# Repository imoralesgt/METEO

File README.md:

# METEO
## TFM MSEEI Universidad de Malaga
## Iván René Morales Argueta - 2018

===========================================================

# ToDo List
## Meteo
- [x] Connect to MQTT Broker in object constructor
	* [x] Subscribe to each ```Settings``` sub-topic ```Settings/#```
	* [ ] \(Optional) _Show performance and broker info by subscribing to special $SYS topics (https://www.hivemq.com/blog/mqtt-essentials-part-5-mqtt-topics-best-practices)_
- [x] Sample each sensor using separate threads
	* [x] Create a generic sampling method (one-shot), which receives the sensor name as parameter
		- [x] ```sampleSensor (sensorName)```
		- [x] Front-end interface variables (i.e. Air Quality, instead of Humidity+Gas_Resistance)
	- [x] Create a thread/method to periodically launch the one-shot sampling method
	* [x] Generate as many threads running this method as required
	* [ ] ~~Kill sampling threads during object destruction~~ Destructor not compatible with threaded implementation
	* [X] Implement a mutual-exclusion mechanism to avoid access violations
- [x] Send sensors' data via MQTT using topics to distribute data into different channels
- [x] Each "METEO" station MUST have a vaild (integer type) identifier, starting from 0
- [x] Topics should accomplish with the following template:
	* [x] ```METEO/<stationNumber>/Data/<sensor>```
	* [x] Valid ```<stationNumber>``` (identifiers) are integers from 0 to N-1
	* [x] Valid ```<sensor>``` values are:
		- [x] Temperature (Environmental temperature) [temp]
		- [x] Humidity (Relative humidity) [hum]
		- [x] Pressure (Local atmospheric pressure) [pres]
		- [x] Light (Incident light measurement) [light]
		- [x] AirQuality (Air quality as pollution measurement) [airQ]
		- [ ] ~~PPM (Raw particle count) [ppm]~~ PPM is irrelevant. Instead, PPM field used to transmit raw gas resistance value
- [x] A special topic may be used to set/get the sampling period dymanically
	* [x] ```METEO/<stationNumber>/Settings/SamplingRate/<sensor>```
	* [x] ```<sensor>``` field (sub-topic) is the same as described before
	* [x] Sampling rate value must be validated to remain between a valid range
		- [x] Min sampling rate 1 minute
		- [x] Max sampling rate 120 minutes
		- [x] If a sampling rate (SR) out of these limits is set, a default value will be chosen if a prior valid SR wasn't set yet; otherwise, the last valid SR will remain active
- [ ] \(Optional) _A special topic may be used to remotely reboot the device if no Alive beacons have been received_
	- [ ] _```METEO/<stationNumber>/Setiings/Reboot```_
	- [ ] _A unique key must be sent as password (through ```Reboot``` topic) to force a reboot_
	- [ ] _Key will be ```stationNumber```-dependent and time-dependent (unix format) hash_
	- [ ] _Hash must be computed by UI_
- [x] A special topic may be used to announce "I'm Alive" messages from stations to broker
	* [x] Invoke it via a separate thread as it may behave as a locking method
	* [x] ```METEO/Alive```
	* [x] Each station should publish a message containing only its ```<stationNumber>``` periodically (ie. every 1 minute)

## Printed circuit board
- [x] Design a PCB to place the sensor boards and the User-Interaction hardware (push-button + LED)
	- [x] Design must be compatible with Raspberry PI 3 header footprint
	- [x] Power must be supplied from Raspberry PI's 3v3/GND breakout pins
	- [x] Manufacture PCB and test functionality

## BME680_METEO
- [x] Compute Air Quality (%) using Humidity and Gas measurements
- [ ] ~~Compute PPM using Gas Baseline and Gas measurements~~ Not a requirement. Discarded from further releases.

## User Interaction
- [x] Add an LED status indicator to show whether the server is running or not (using RPI-GPIO)
- [x] Add a push-button input to hard-reset the server via a separate thread if anything fails (using RPI-GPIO)

## Data management
- [x] Grab sensors' data from MQTT broker and process it to deliver filtered information 
- [x] Store the processed data into a SQLite database
- [x] Retreive data from Broker and append it to a table within in the DB (running in parallel thread?)
- [x] Export table's content to a CSV when required
- [x] If several measurements from different sensors retreived within the same MINUTE, store them in the same register row.
- [x] If several measurements form the same sensor retreived within the same MINUTE, average grabbed values and then store the last average computation.

## Reliability
- [x] Run meteo.py as a standalone application
	- [x] Set flag to meteo.py
		- [x] ```chmod +x meteo.py```
- [x] Autorun on boot
	- [x] ```sudo crontab -e```
	- [x] ```@reboot /home/pi/METEO/meteo.py &```
- [x] Software Watchdog Timer
	- [x] Run a parallel process (subscribed to ```ALIVE``` topic) to check whether METEO is running or not
	- [x] Restart METEO process after 3 consecutive ```ALIVE``` periods with no answer
	- [x] Start WDT timer after the first ```ALIVE``` message arrives

# User interface
- [x] Node-RED User Interface

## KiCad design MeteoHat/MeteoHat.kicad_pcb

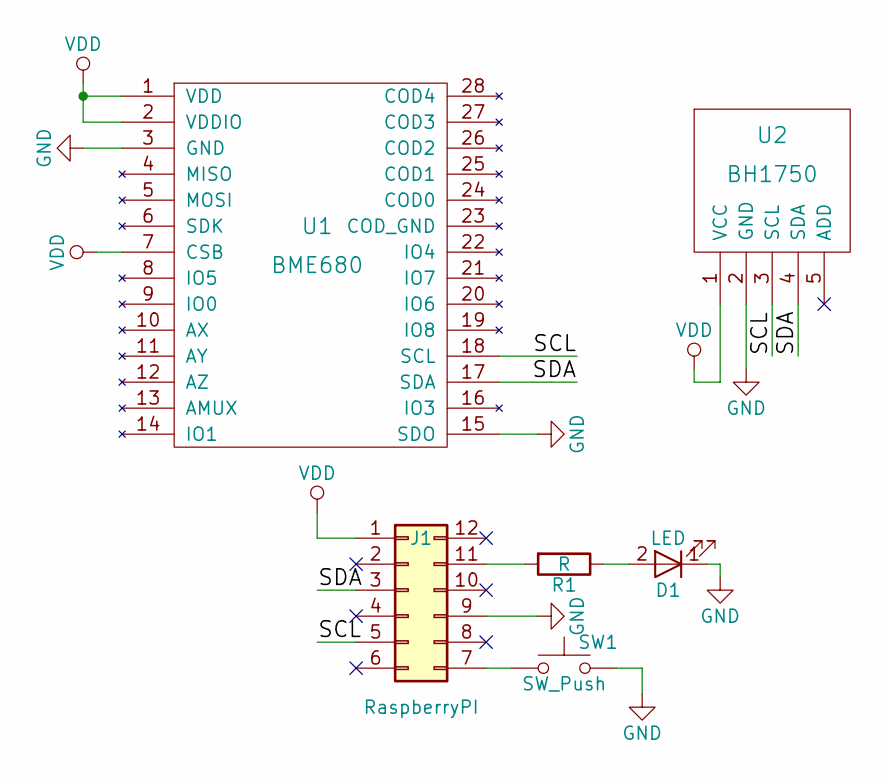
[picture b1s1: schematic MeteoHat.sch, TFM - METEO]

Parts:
D1: LED; LED_1206_HandSoldering
J1: RaspberryPI; Pin_Header_Straight_2x06_Pitch2.54mm
R1: R; R_0805_HandSoldering
SW1: SW_Push; 3x6x2.5mm_tact_switch
U1: BME680
U2: BH1750

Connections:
/SCL: J1.5, U1.18 (SCL), U2.3 (SCL)
/SDA: J1.3, U1.17 (SDA), U2.4 (SDA)
GND: D1.1 (K), J1.9, SW1.2, U1.3 (GND), U1.15 (SDO), U2.2 (GND)
unnamed: D1.2 (A), R1.1
unnamed: J1.7, SW1.1
unnamed: J1.11, R1.2
VDD: J1.1, U1.1 (VDD), U1.2 (VDDIO), U1.7 (CSB), U2.1 (VCC)

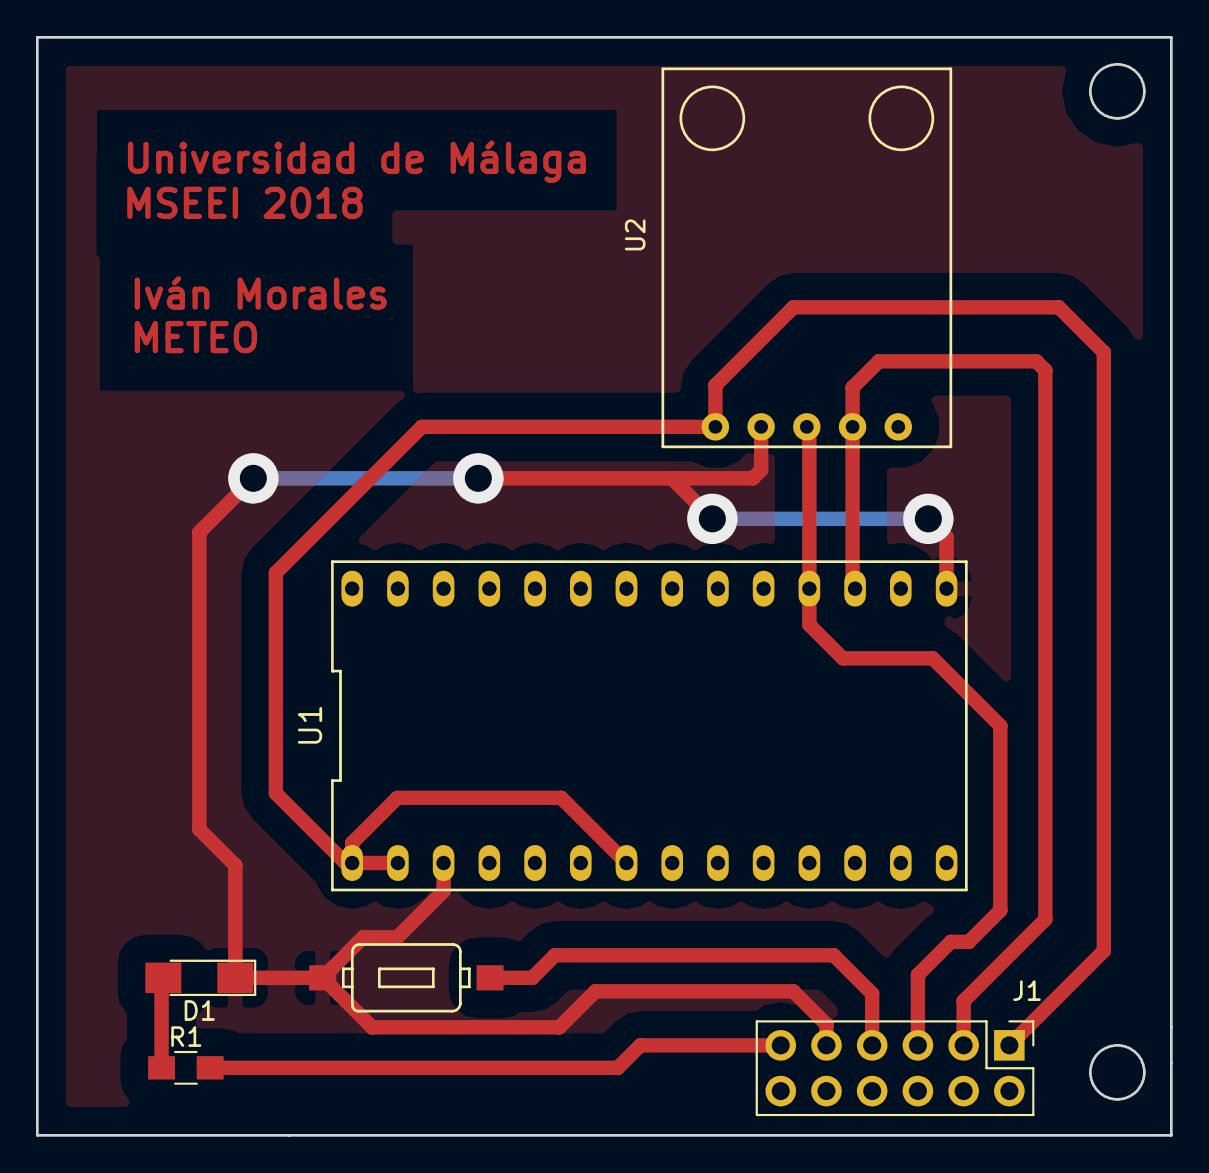
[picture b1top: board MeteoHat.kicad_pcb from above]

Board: 2 copper layers, 63.0 x 61.0 mm, 6 parts (0 on the bottom side), 7 nets.

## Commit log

2018-06-16 Initial repo setup
    Also added Sublime SFTP auto-upload config
2018-06-16 First BME680 test
    BME680 Interface Class for METEO first Test
2018-06-18 Added non-blocking gas sensor burn-in daemon
    - The rest of the sensors start measuring immediately after BME680 is initialized. Gas sensor is burned-up until burn-in time (default: 5 minutes) pass by.
    - Added external constants file for easy sensor configuration (sensorDefs.py).
    - Class was completely reordered to easily accomodate further changes in a much more robust and modular way.
2018-06-20 Moved class-related globals before constructor
2018-06-20 Added some comments
2018-06-20 Added light sensor import
2018-06-20 BH1750 low level library from oskar456
    https://gist.github.com/oskar456/95c66d564c58361ecf9f
2018-06-20 Added light sensor-related defines
2018-06-20 BH1750 Light sensor high level fault-tolerant library
    Default 0.5 lux resolution and 0x23 I2C Address Map
2018-06-23 Added Endline
2018-06-23 Added KeyboardInterrupt Exception handling in test mode
    Also added comments
2018-07-02 Work started under METEO main class
    - Requirements have been defined in the initial comments
    - Standarization of available sensors and sampling rate manipulation methods have been written
    - MQTT Client connection to broker has been implemented, including service restart if connection to broker fails
2018-07-12 Fixed some typos in the comments
2018-07-13 Added requirements to the TODO list
2018-07-14 PCB for Raspberry PI Hat
2018-07-14 Some minor tests done with MQTT Broker
2018-07-14 TODO list updated
2018-07-14 Fixed Readme format
2018-07-14 Fixed Readme tabs
2018-07-14 Added checkboxes to each item in the "ToDo" list
2018-07-14 Added optional requirements
2018-07-15 Fixed BME680 HAL to support threading
2018-07-15 Added some error definitions
2018-07-15 Implemented mutual-exclusion (MUTEX) mechanism
    - Implemented MUTEX with/without autoexecution of threads in queue
    - Mutex tests have been passed using a shared resource (BME680) in up to 20 (MAX_TASKS) concurrent threads where temperature was measured
    - Implemented one-shot measurement of front-end variables (temperature, air quality, ppm, presure, humidity, luminosity), which relay on back-end variables (gas resistor, thermometer, etc)
2018-07-16 Station number can be set in defs file
2018-07-16 MQTT Subscription/Publishing functionality added
    - Sampling rate can be individualy set for each sensor
    - Publishing sensor values still not working, mutex implemented and tested
2018-07-23 Fixed unsampled sensors Null data, now returning False if no sensor data available
2018-07-23 Sensor data published in separate threads as described in requirements
2018-07-24 Default sampling rate is now 5 minutes
2018-07-24 Debugging disabled in main METEO script
2018-07-24 Implemented Air Quality Index computation (IAQ). PPM is irrelevant
    IAQ in a 0 to 500 range, where 500 is worst.
    PPM measurements used to display raw gas resistance value
2018-07-25 Added RPi GPIO-based Low-levelUser Interaction with LED and Push-Button
2018-07-25 Showing via LED broker connection status
    LED On: Connected to broker
    LED Off: Disconnected from broker
2018-07-25 Added PCB Keepout Zones
2018-07-26 Added reboot feature while depressing push button during 30 seconds
    METEO Autorun has been enabled during boot time
2018-07-28 Fixed BME680 max gas sensor resistance value
2018-07-28 Fixed typo
2018-07-28 First WDT commit as a class implementation
    Still needs to be tested
2018-07-28 User-defined settings in 'defs.py' file now easier to modify
    User can now easily modify 'defs.py' file to setup METEO station parameters, such as broker address/port and sampling rate ranges.
2018-07-28 Fixed BME680 gas resistance range
2018-07-28 Tests sent to a different location
2018-07-28 Setup User Interaction for standalone execution
2018-07-28 Fixed and tested WDT implementation
2018-07-31 First GUI commit
    Using Node-RED with Dashboard controls.
    - Displays real time data
    - Displays historic graph
    - Sampling rate (SR) can be changed from gui
    - Coherence of SR display (if changed in from a different device, displayed value changes too)
2018-08-01 Fixed typo in comments
2018-08-01 WDT Not Daemon anymore
2018-08-01 Storage Class first commit
    Secondary methods for file management and MQTT subscription, as well as date/time gathering implemented.
2018-08-02 Implemented StorageQueue - Not tested yet
    StorageQueue to avoid leaving register fields in blank if data arrives within a 1 minute window.
2018-09-02 Fixed bugs. Now writting to register data in sync
    SQL Implementation left. However, data is already formatted and gathered so it shouldn't be a big deal. Old data deletition every new day still needs to be implemented.
2018-09-03 Fixed "uncleaned" queues
2018-09-04 Fixed unsent data to register queue
2018-09-08 SQLite 3 DB support added
    Now data is stored in meteo.db SQLIte3 data base and then exported to meteo.csv
2018-09-09 DB Feature added: now deletes old records (31 days or more old)
    Not tested yet
2018-09-10 Fixed paths for autostart on boot
    Now working everything, storing data and deleting old records.
    Only Node-Red FTP CSV File download missing.
2018-09-12 Not debugging DB anymore
2018-09-12 NodeRed UI
2018-09-12 __main.py__ now required anymore
2018-09-12 Storage launched as a thread, not as a parallel process anymore
2018-09-13 METEO Autostart triggered from NodeRed
2018-09-15 Project Done
    Documentation in progress...
2018-09-16 Fixed default sampling rate | Reduced ALIVE beacon period downto 30 seconds | Added sh startup script | Backed Node-Red UI up
2018-09-17 Small fixes to test subsystems' functionality
